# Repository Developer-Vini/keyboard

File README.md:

# Keyboard

This project is a 75% mechanical keyboard that I developed from scratch using KiCad. The idea was to create a compact, functional, and relatively simple keyboard, retaining the main keys of a conventional keyboard without taking up too much desk space.
The project was designed to be a real physical keyboard, so I didn't just focus on the visual aspect: I developed the circuit board (PCB), organized the key matrix, defined the electrical connections, and chose the necessary components so that the keyboard can be assembled and used later.

This project was going to be submitted to the Fabricate program, but I decided against it; I'll post it here instead. Because I thought halfway through, I have several other things to do, it's better not to. I didn't end up submitting it!

# Layout 
The keyboard uses a 75% layout, which retains virtually all the important functions of a full keyboard, but eliminates the spacebar and some less frequently used keys.
It has the main letter, number, and symbol keys, as well as keys such as the arrow keys, Shift, Ctrl, Alt, Enter, Backspace, and other function keys.

# Case

# PCB

The entire board was designed in KiCad. First, I arranged the keys according to the chosen layout and then started working on the electrical part.
The keys are part of a matrix of rows and columns. This way, it's not necessary to connect each key directly to a separate microcontroller pin. Each switch is connected to the matrix, allowing the microcontroller to identify which key was pressed.
I also added the components necessary for the correct reading of the matrix, including the diodes associated with the keys.

# Scheme

# Parts used for the project:

## Raspberry Pi Pico
The keyboard has a microcontroller responsible for reading the key matrix and transforming the keystrokes into commands that the computer can interpret.

## Diode 1N4148

## Stabilizers

## Switchs

## Keycaps

## USB-c Cable

# BOM

| Quantity      | Parts         | Description   | Suppliers     | Price         |
| ------------- | ------------- | ------------- | ------------- | ------------- |
| 1x  | RaspberryPi Pico  | This will be the main part of the keyboard—the component that actually makes it function and respond to all of the user's commands.  | [RaspberryPi Pico](https://www.google.com/aclk?sa=L&ai=DChsSEwibxe-8_9eXAxX4VUgAHYpNKHsYACICCAEQChoCY2U&co=1&ase=2&gclid=CjwKCAjw9PvWBhAxEiwAddzYyYSJZ7UXpklbmFzkP8O3EFmvRU4AtTAiUxpHr_9tkhAvw0_RXMD6dxoCH_UQAvD_BwE&cid=CAAS9QHkaBhD6FbWmHBN7MsDVew-0O9MhhjhIk7VtOfQ49BJhjWOsTSFw6bp9yYYFJ5JKXmd-5HlOupdWXErJn4rQBD4zEQBMx2k93VtfnZNmJsqhQl4dindNntgzA1MGSygfU4WBlBbf2g3GR71w-paDlBHAieKfWmn8Q8aF84Z_ALl27jHaUSn44IKSyyzx1Ctnc0VlIKf7s117n3O0QQEuqRqYpVqkuyavaDcBinwQSb-BUZyAK75_QBhayI-lT0iP4xrCdrz7IJu-AcpH4WNwdGSV32M8N-7CmS_lCGfJiR7hDXAUFte0_lgmTn8vMXgSMeHjBBceA&cce=2&category=acrcp_v1_32&sig=AOD64_3wK0zsBjN2-6bpFfc1b0CkzevsDA&ctype=5&q=&nis=4&ved=2ahUKEwjZgei8_9eXAxWoHrkGHQ5hHygQ5bgDKAB6BAgOEAs&adurl=) | $6.2  |
| 87x | Diode 1N4148  | The diode serves to prevent double-clicking and the ghosting effect on the keyboard. | [Diode 1N4148](https://www.mercadolivre.com.br/kit-10-diodos-retificadores-1n4148-1000v-02a-stg-eletro-vidro-passivado/p/MLB27103607?pdp_filters=item_id%3AMLB3798508313&from=gshop&matt_tool=56164162&matt_word=&matt_source=google&matt_campaign_id=22090193744&matt_ad_group_id=194474654154&matt_match_type=&matt_network=g&matt_device=c&matt_creative=792355615410&matt_keyword=&matt_ad_position=&matt_ad_type=pla&matt_merchant_id=735098660&matt_product_id=MLB27103607-product&matt_product_partition_id=2495059736147&matt_target_id=aud-1967662333334:pla-2495059736147&cq_src=google_ads&cq_cmp=22090193744&cq_net=g&cq_plt=gp&cq_med=pla&gad_source=1&gad_campaignid=22090193744&gbraid=0AAAAAD93qcAFXS1D6HAsi0Wi-mlFE3ZrU&gclid=CjwKCAjw9PvWBhAxEiwAddzYydhtHdCHVoedVGiZSYBDaSSydb0Fx_Z1XWSCBVeinyjqGIG87Sv_yRoC2DcQAvD_BwE)  |  $8  |
| 4x | Stabilizers | As the name itself suggests, this is a stabilizer. Since some parts are larger, this is used to keep them from wobbling. | [Stabilizers](https://pt.aliexpress.com/item/1005011961905061.html?spm=a2g0o.productlist.main.2.77404c8agv3Zpj&algo_pvid=c416a962-3552-4e1e-b0d2-356b99ff4161&algo_exp_id=c416a962-3552-4e1e-b0d2-356b99ff4161-1&pdp_ext_f=%7B%22order%22%3A%2261%22%2C%22eval%22%3A%221%22%2C%22fromPage%22%3A%22search%22%7D&pdp_npi=6%40dis%21BRL%2138.51%2138.51%21%21%2147.64%2147.64%21%402101c69517930290229327326e0f42%2112000057150856776%21sea%21BR%210%21ABX%211%210%21n_tag%3A-29910%3Bd%3A4e7cc88e%3Bm03_new_user%3A-29895&curPageLogUid=fAcMEu0ju6qA&utparam-url=scene%3Asearch%7Cquery_from%3A%7Cx_object_id%3A1005011961905061%7C_p_origin_prod%3A) | $10.5  |
| 88x | Switchs  | This component is what allows commands to be sent to the controller, indicating which key the user wants to press. | [Switchs](https://www.mercadolivre.com.br/kit-10-clicker-teclado-mecanico-azul-3-pinos-switch-gamer/up/MLBU4799799250?pdp_filters=item_id%3AMLB7442852240&from=gshop&matt_tool=31485049&matt_word=&matt_source=google&matt_campaign_id=22090354244&matt_ad_group_id=191786791161&matt_match_type=&matt_network=g&matt_device=c&matt_creative=782869963634&matt_keyword=&matt_ad_position=&matt_ad_type=pla&matt_merchant_id=5756723143&matt_product_id=MLBU4799799250&matt_product_partition_id=2498613880064&matt_target_id=aud-1967662333334:pla-2498613880064&cq_src=google_ads&cq_cmp=22090354244&cq_net=g&cq_plt=gp&cq_med=pla&gad_source=1&gad_campaignid=22090354244&gbraid=0AAAAAD93qcCIKBSjcXEdc9_dg7ThbMKog&gclid=CjwKCAjw9PvWBhAxEiwAddzYyTBkgcE5iz3weebgTrAdZ9NQqK1G1vc-NDPvYyXmfEVYPgfHyPvkehoC4xEQAvD_BwE) |  $34  |
| 88x | Keycaps  | This is basically the part you’ll be able to click on; without it, you’d just have a bunch of random pins that don’t make any sense lol | [Keycaps](https://www.mercadolivre.com.br/kit-de-keycaps-redragon-degrade-verde-abnt2-106-teclas-abs/p/MLB54150952?pdp_filters=item_id%3AMLB4289903217&from=gshop&matt_tool=83591963&matt_word=&matt_source=google&matt_campaign_id=22090193903&matt_ad_group_id=194474632074&matt_match_type=&matt_network=g&matt_device=c&matt_creative=792355616043&matt_keyword=&matt_ad_position=&matt_ad_type=pla&matt_merchant_id=735128761&matt_product_id=MLB54150952-product&matt_product_partition_id=2496085499453&matt_target_id=aud-1967662333334:pla-2496085499453&cq_src=google_ads&cq_cmp=22090193903&cq_net=g&cq_plt=gp&cq_med=pla&gad_source=1&gad_campaignid=22090193903&gbraid=0AAAAAD93qcCRuFOxaXQNEiNnHxQu-nWmm&gclid=CjwKCAjw9PvWBhAxEiwAddzYyQF_TCt68xujzzVDeMJ7RKth2i88PenlMMTJps7kogIt2-d3XBUaTBoCNakQAvD_BwE) |  $16  |
| 1x | USB-C cable  | Without this, the keyboard won't work, as it won't receive any charge. | [USB-C Cable](https://produto.mercadolivre.com.br/MLB-6128401728-cabo-coiled-teclado-mecnico-usb-tipo-c-conector-aviador-_JM?matt_tool=56164162&matt_word=&matt_source=google&matt_campaign_id=22090193744&matt_ad_group_id=194474654154&matt_match_type=&matt_network=g&matt_device=c&matt_creative=792355615410&matt_keyword=&matt_ad_position=&matt_ad_type=pla&matt_merchant_id=296849702&matt_product_id=MLB6128401728&matt_product_partition_id=2495059736307&matt_target_id=aud-1967662333334:pla-2495059736307&cq_src=google_ads&cq_cmp=22090193744&cq_net=g&cq_plt=gp&cq_med=pla&gad_source=1&gad_campaignid=22090193744&gbraid=0AAAAAD93qcAFXS1D6HAsi0Wi-mlFE3ZrU&gclid=CjwKCAjw9PvWBhAxEiwAddzYyeyiGedMsmeVZ_o-1LvWcwa25IfkgyL4xbatIPCuwWQzTEjeJqRTXBoCOCsQAvD_BwE) | $13.46 |
| total cost:     | - |  Some are all-inclusive—shipping and everything—but others aren't. You only find out once you add everything to your cart.| - | 88,16|

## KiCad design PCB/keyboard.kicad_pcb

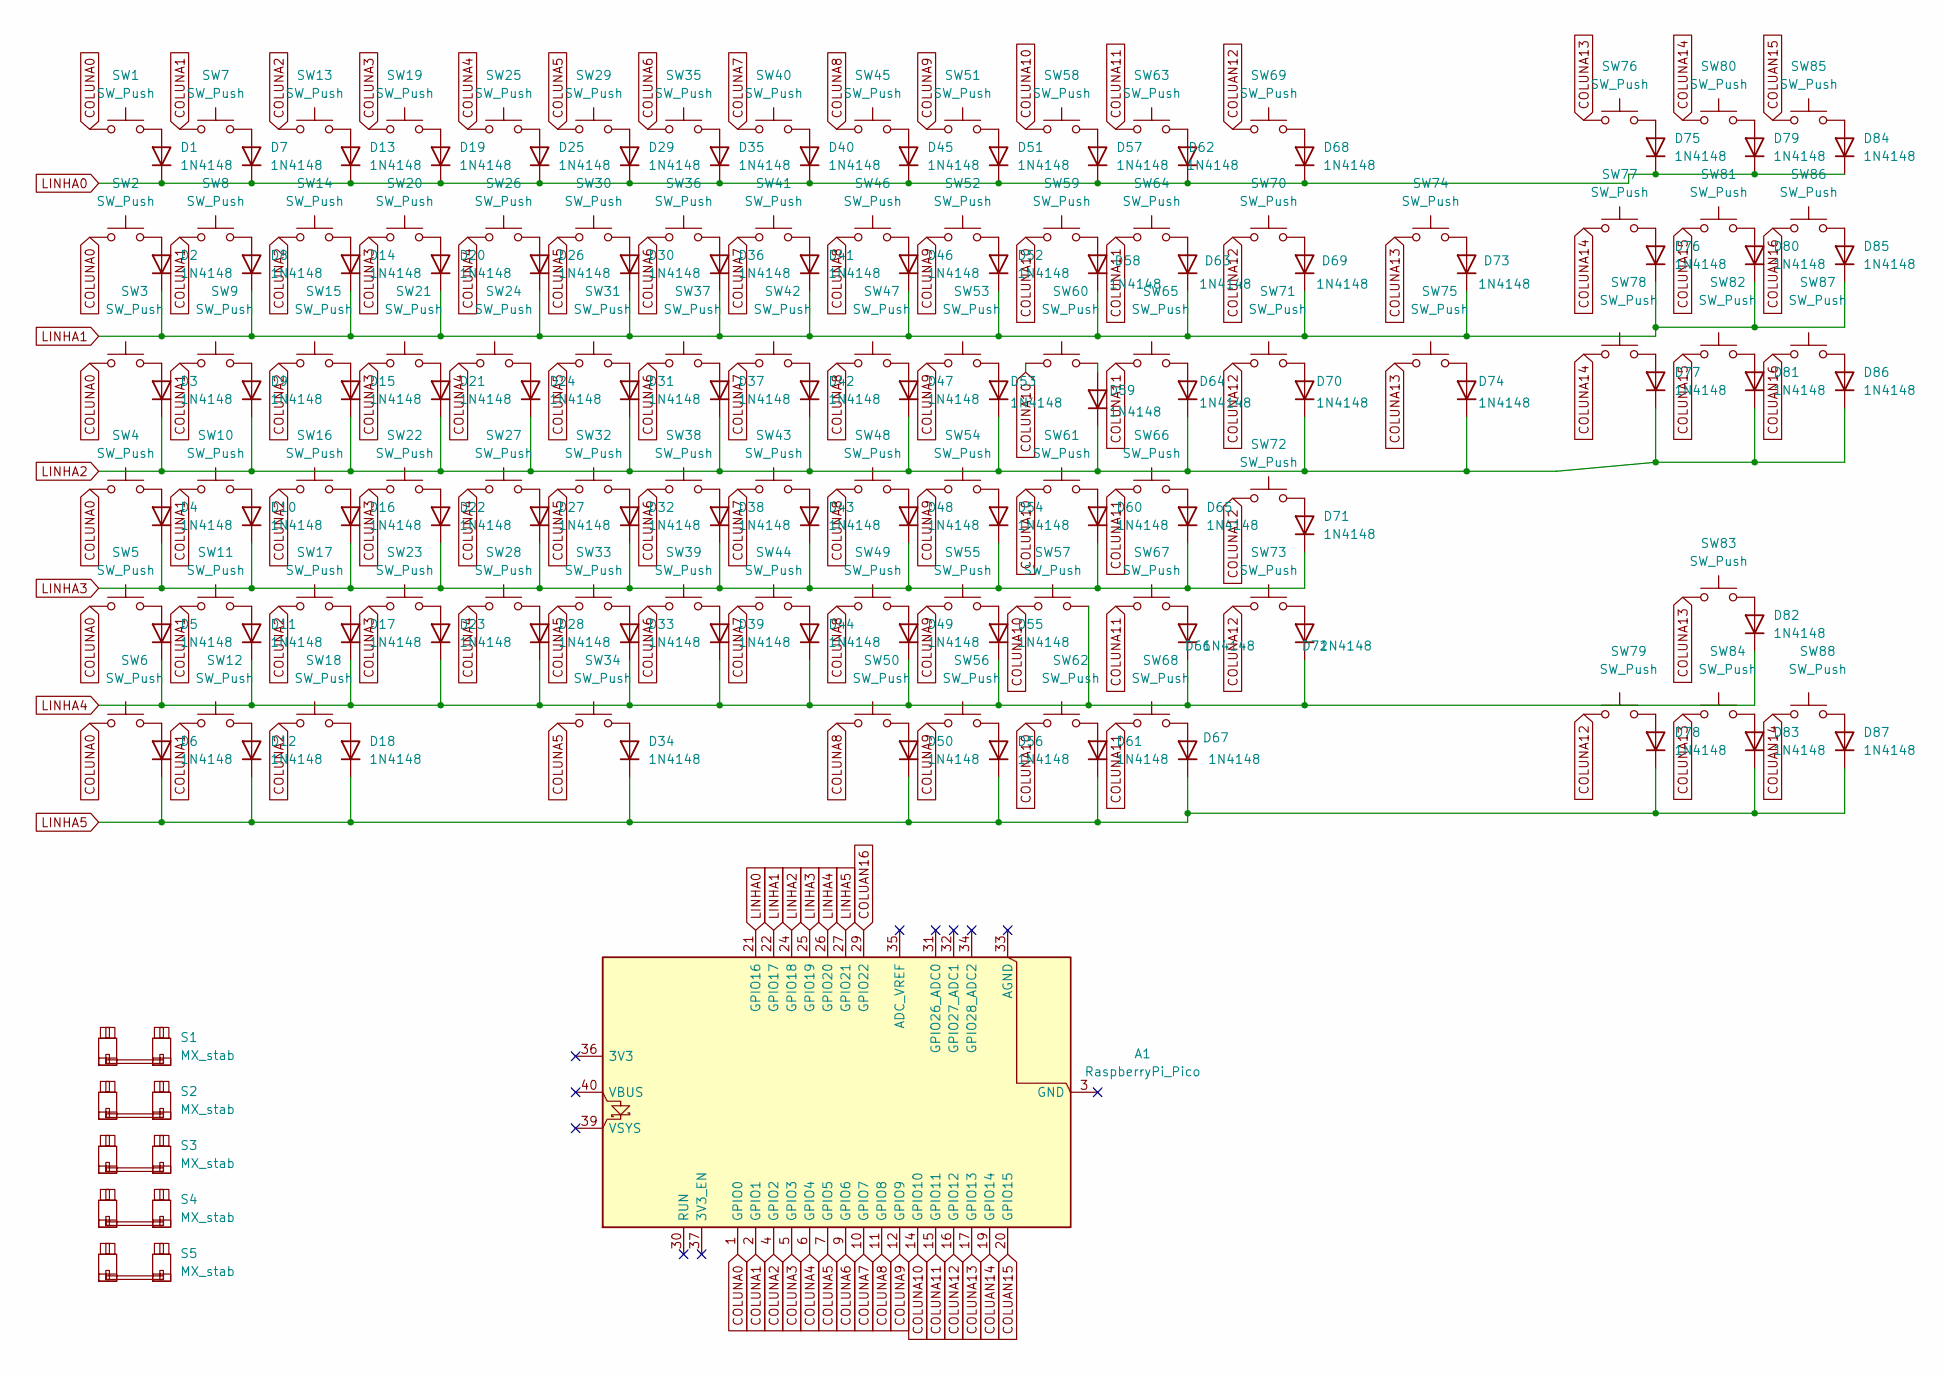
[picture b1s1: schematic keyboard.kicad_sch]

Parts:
A1: RaspberryPi_Pico; RaspberryPi_Pico_Common_THT
D1, D2, D3, D4, D5, D6, D7, D8, D9, D10, D11, D12, D13, D14, D15, D16, D17, D18, D19, D20, D21, D22, D23, D24, D25, D26, D27, D28, D29, D30, D31, D32, D33, D34, D35, D36, D37, D38, D39, D40, D41, D42, D43, D44, D45, D46, D47, D48, D49, D50, D51, D52, D53, D54, D55, D56, D57, D58, D59, D60, D61, D62, D63, D64, D65, D66, D67, D68, D69, D70, D71, D72, D73, D74, D75, D76, D77, D78, D79, D80, D81, D82, D83, D84, D85, D86, D87: 1N4148; D_DO-35_SOD27_P7.62mm_Horizontal
S1, S2, S3, S4, S5: MX_stab; STAB_MX_P_6.25u
SW1, SW2, SW3, SW4, SW5, SW6, SW7, SW8, SW9, SW10, SW11, SW12, SW13, SW14, SW15, SW16, SW17, SW18, SW19, SW20, SW21, SW22, SW23, SW24, SW25, SW26, SW27, SW28, SW29, SW30, SW31, SW32, SW33, SW34, SW35, SW36, SW37, SW38, SW39, SW40, SW41, SW42, SW43, SW44, SW45, SW46, SW47, SW48, SW49, SW50, SW51, SW52, SW53, SW54, SW55, SW56, SW57, SW58, SW59, SW60, SW61, SW62, SW63, SW64, SW65, SW66, SW67, SW68, SW69, SW70, SW71, SW72, SW73, SW74, SW75, SW76, SW77, SW78, SW79, SW80, SW81, SW82, SW83, SW84, SW85, SW86, SW87, SW88: SW_Push; SW_MX_1u

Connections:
COLUAN14: A1.19 (GPIO14), SW88.1
COLUAN15: A1.20 (GPIO15), SW85.1
COLUAN16: A1.29 (GPIO22), SW86.1, SW87.1
COLUNA0: A1.1 (GPIO0), SW1.1, SW2.1, SW3.1, SW4.1, SW5.1, SW6.1
COLUNA1: A1.2 (GPIO1), SW7.1, SW8.1, SW9.1, SW10.1, SW11.1, SW12.1
COLUNA2: A1.4 (GPIO2), SW13.1, SW14.1, SW15.1, SW16.1, SW17.1, SW18.1
COLUNA3: A1.5 (GPIO3), SW19.1, SW20.1, SW21.1, SW22.1, SW23.1
COLUNA4: A1.6 (GPIO4), SW24.1, SW25.1, SW26.1, SW27.1, SW28.1
COLUNA5: A1.7 (GPIO5), SW29.1, SW30.1, SW31.1, SW32.1, SW33.1, SW34.1
COLUNA6: A1.9 (GPIO6), SW35.1, SW36.1, SW37.1, SW38.1, SW39.1
COLUNA7: A1.10 (GPIO7), SW40.1, SW41.1, SW42.1, SW43.1, SW44.1
COLUNA8: A1.11 (GPIO8), SW45.1, SW46.1, SW47.1, SW48.1, SW49.1, SW50.1
COLUNA9: A1.12 (GPIO9), SW51.1, SW52.1, SW53.1, SW54.1, SW55.1, SW56.1
COLUNA10: A1.14 (GPIO10), SW57.1, SW58.1, SW59.1, SW60.1, SW61.1, SW62.1
COLUNA11: A1.15 (GPIO11), SW63.1, SW64.1, SW65.1, SW66.1, SW67.1, SW68.1
COLUNA13: A1.17 (GPIO13), SW74.1, SW75.1, SW76.1, SW83.1, SW84.1
COLUNA14: SW77.1, SW78.1, SW80.1
COLUNA15: SW81.1, SW82.1
LINHA0: A1.21 (GPIO16), D1.1 (K), D7.1 (K), D13.1 (K), D19.1 (K), D25.1 (K), D29.1 (K), D35.1 (K), D40.1 (K), D45.1 (K), D51.1 (K), D57.1 (K), D62.1 (K), D68.1 (K), D75.1 (K), D79.1 (K), D84.1 (K)
LINHA1: A1.22 (GPIO17), D2.1 (K), D8.1 (K), D14.1 (K), D20.1 (K), D26.1 (K), D30.1 (K), D36.1 (K), D41.1 (K), D46.1 (K), D52.1 (K), D58.1 (K), D63.1 (K), D69.1 (K), D73.1 (K), D76.1 (K), D80.1 (K), D85.1 (K)
LINHA2: A1.24 (GPIO18), D3.1 (K), D9.1 (K), D15.1 (K), D21.1 (K), D24.1 (K), D31.1 (K), D37.1 (K), D42.1 (K), D47.1 (K), D53.1 (K), D59.1 (K), D64.1 (K), D70.1 (K), D74.1 (K), D77.1 (K), D81.1 (K), D86.1 (K)
LINHA3: A1.25 (GPIO19), D4.1 (K), D10.1 (K), D16.1 (K), D22.1 (K), D27.1 (K), D32.1 (K), D38.1 (K), D43.1 (K), D48.1 (K), D54.1 (K), D60.1 (K), D65.1 (K), D71.1 (K)
LINHA4: A1.26 (GPIO20), D5.1 (K), D11.1 (K), D17.1 (K), D23.1 (K), D28.1 (K), D33.1 (K), D39.1 (K), D44.1 (K), D49.1 (K), D55.1 (K), D66.1 (K), D72.1 (K), D82.1 (K), SW57.2
LINHA5: A1.27 (GPIO21), D6.1 (K), D12.1 (K), D18.1 (K), D34.1 (K), D50.1 (K), D56.1 (K), D61.1 (K), D67.1 (K), D78.1 (K), D83.1 (K), D87.1 (K)
unnamed: D1.2 (A), SW1.2
unnamed: D2.2 (A), SW2.2
unnamed: D3.2 (A), SW3.2
unnamed: D4.2 (A), SW4.2
unnamed: D5.2 (A), SW5.2
unnamed: D6.2 (A), SW6.2
unnamed: D7.2 (A), SW7.2
unnamed: D8.2 (A), SW8.2
unnamed: D9.2 (A), SW9.2
unnamed: D10.2 (A), SW10.2
unnamed: D11.2 (A), SW11.2
unnamed: D12.2 (A), SW12.2
unnamed: D13.2 (A), SW13.2
unnamed: D14.2 (A), SW14.2
unnamed: D15.2 (A), SW15.2
unnamed: D16.2 (A), SW16.2
unnamed: D17.2 (A), SW17.2
unnamed: D18.2 (A), SW18.2
unnamed: D19.2 (A), SW19.2
unnamed: D20.2 (A), SW20.2
unnamed: D21.2 (A), SW21.2
unnamed: D22.2 (A), SW22.2
unnamed: D23.2 (A), SW23.2
unnamed: D24.2 (A), SW24.2
unnamed: D25.2 (A), SW25.2
unnamed: D26.2 (A), SW26.2
unnamed: D27.2 (A), SW27.2
unnamed: D28.2 (A), SW28.2
unnamed: D29.2 (A), SW29.2
unnamed: D30.2 (A), SW30.2
unnamed: D31.2 (A), SW31.2
unnamed: D32.2 (A), SW32.2
unnamed: D33.2 (A), SW33.2
unnamed: D34.2 (A), SW34.2
unnamed: D35.2 (A), SW35.2
unnamed: D36.2 (A), SW36.2
unnamed: D37.2 (A), SW37.2
unnamed: D38.2 (A), SW38.2
unnamed: D39.2 (A), SW39.2
unnamed: D40.2 (A), SW40.2
unnamed: D41.2 (A), SW41.2
unnamed: D42.2 (A), SW42.2
unnamed: D43.2 (A), SW43.2
unnamed: D44.2 (A), SW44.2
unnamed: D45.2 (A), SW45.2
unnamed: D46.2 (A), SW46.2
unnamed: D47.2 (A), SW47.2
unnamed: D48.2 (A), SW48.2
unnamed: D49.2 (A), SW49.2
unnamed: D50.2 (A), SW50.2
unnamed: D51.2 (A), SW51.2
unnamed: D52.2 (A), SW52.2
unnamed: D53.2 (A), SW53.2
unnamed: D54.2 (A), SW54.2
unnamed: D55.2 (A), SW55.2
unnamed: D56.2 (A), SW56.2
unnamed: D57.2 (A), SW58.2
unnamed: D58.2 (A), SW59.2
unnamed: D59.2 (A), SW60.2
unnamed: D60.2 (A), SW61.2
unnamed: D61.2 (A), SW62.2
unnamed: D62.2 (A), SW63.2
unnamed: D63.2 (A), SW64.2
unnamed: D64.2 (A), SW65.2
unnamed: D65.2 (A), SW66.2
unnamed: D66.2 (A), SW67.2
unnamed: D67.2 (A), SW68.2
unnamed: D68.2 (A), SW69.2
unnamed: D69.2 (A), SW70.2
unnamed: D70.2 (A), SW71.2
unnamed: D71.2 (A), SW72.2
unnamed: D72.2 (A), SW73.2
unnamed: D73.2 (A), SW74.2
unnamed: D74.2 (A), SW75.2
unnamed: D75.2 (A), SW76.2
unnamed: D76.2 (A), SW77.2
unnamed: D77.2 (A), SW78.2
unnamed: D78.2 (A), SW79.2
unnamed: D79.2 (A), SW80.2
unnamed: D80.2 (A), SW81.2
unnamed: D81.2 (A), SW82.2
unnamed: D82.2 (A), SW83.2
unnamed: D83.2 (A), SW84.2
unnamed: D84.2 (A), SW85.2
unnamed: D85.2 (A), SW86.2
unnamed: D86.2 (A), SW87.2
unnamed: D87.2 (A), SW88.2

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
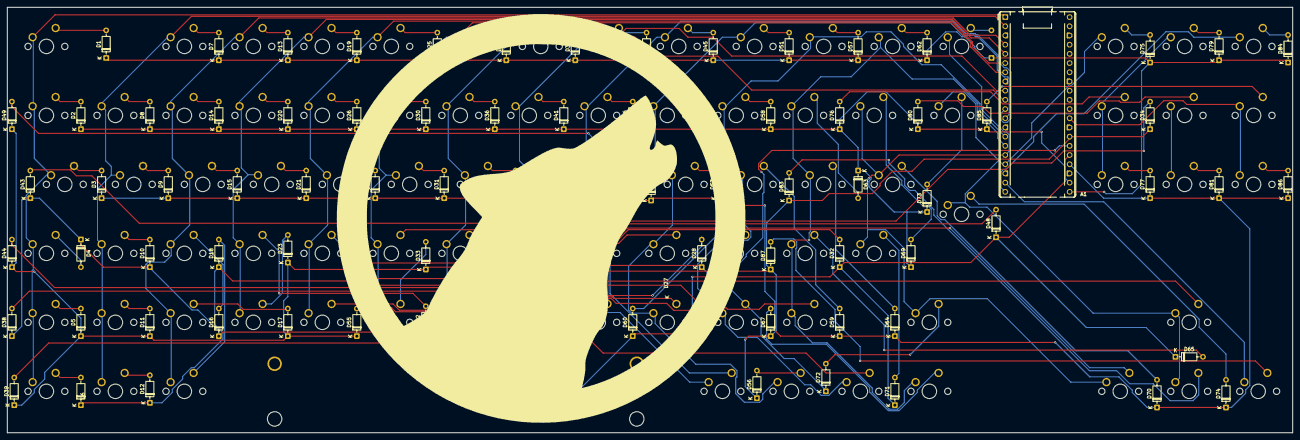
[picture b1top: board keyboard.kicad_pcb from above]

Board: 2 copper layers, 355.0 x 117.5 mm, 177 parts (1 on the bottom side), 112 nets.

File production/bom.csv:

Designator,Footprint,Quantity,Value,LCSC Part #
A1,RaspberryPi_Pico_Common_THT,1,RaspberryPi_Pico,
"D1, D10, D11, D12, D13, D14, D15, D16, D17, D18, D19, D2, D20, D21, D22, D23, D24, D25, D26, D27, D28, D29, D3, D30, D31, D32, D33, D34, D35, D36, D37, D38, D39, D4, D40, D41, D42, D43, D44, D45, D46, D47, D48, D49, D5, D50, D51, D52, D53, D54, D55, D56, D57, D58, D59, D6, D60, D61, D62, D63, D64, D65, D66, D67, D68, D69, D7, D70, D71, D72, D73, D74, D75, D76, D77, D78, D79, D8, D80, D81, D82, D83, D84, D85, D86, D87, D9",D_DO-35_SOD27_P7.62mm_Horizontal,87,1N4148,
S3,STAB_MX_P_6.25u,1,MX_stab,
"SW1, SW10, SW11, SW12, SW13, SW14, SW15, SW16, SW17, SW18, SW19, SW2, SW20, SW21, SW22, SW23, SW24, SW25, SW26, SW27, SW28, SW29, SW3, SW30, SW31, SW32, SW33, SW34, SW35, SW36, SW37, SW38, SW39, SW4, SW40, SW41, SW42, SW43, SW44, SW45, SW46, SW47, SW48, SW49, SW5, SW50, SW51, SW52, SW53, SW54, SW55, SW56, SW57, SW58, SW59, SW6, SW60, SW61, SW62, SW63, SW64, SW65, SW66, SW67, SW68, SW69, SW7, SW70, SW71, SW72, SW73, SW74, SW75, SW76, SW77, SW78, SW79, SW8, SW80, SW81, SW82, SW83, SW84, SW85, SW86, SW87, SW88, SW9",SW_MX_1u,88,SW_Push,
